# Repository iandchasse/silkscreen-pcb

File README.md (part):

# Silkscreen

**An open-source, open-hardware e-reader mainboard.**

Silkscreen is an open e-paper development board. You can build a pocket reader around it,
adapt its firmware or extend the electronics; this repository covers the mainboard. A factory
can assemble the board for you, and you add a compatible e-paper display, battery, microSD card
and case. It is a 2-layer ESP32-S3 board with a 24-pin display connector,
optional touch and frontlight, microSD and single-cell Li-ion/LiPo power.

It is the successor to [de-link](https://de-link.me). The de-link project hub's pages and photos
are kept on the [`de-link-old`](https://github.com/iandchasse/silkscreen-pcb/tree/de-link-old)
branch. I designed Silkscreen in KiCad 9, but
**you do not need KiCad to order a board.** Every file a factory asks for is in the
`production/` folder of this repository, ready to upload.

| Back (all components) | Front (silkscreen art) |
|:---:|:---:|
|  |  |

## What it is

- **Brain:** an ESP32-S3 module with 16 MB of flash and 8 MB of PSRAM, with USB built in. You
  plug a USB-C cable straight into it, no adapter.
- **Screen:** a 24-pin connector for SPI e-paper panels. The primary target is Good Display's
  4.26" panel family, in plain, touch, frontlight, or touch + frontlight versions. The plain panel
  is sold as `GDEY0426T82`; the others are `GDEQ0426T82` with a suffix for the variant (`-T01C`
  touch, `-FL01C` front light, `-FT01C` both), so always order by the full part number.
- **Power:** charges and runs from a single-cell Li-ion/LiPo pack over USB-C, with charger,
  cell protection and a 3.3 V regulator on board. The charger is a TI BQ21040: about 115 mA, which
  takes about 5 hours for a 500 mAh pack, and only between about 0 and 41 °C, measured by a
  thermistor on the board. Power it from a 5 V source only.
- **Temperature:** 0 to 50 °C in use, a limit set by the display panel.
- **Storage:** a push-push microSD socket.
- **Buttons:** eight page/navigation buttons, plus power and reset.
- **Size:** 60.05 × 111.30 mm, 1.6 mm thick. Every part is soldered onto the **back** face, so
  the front is clear for the display.

Silkscreen is built to run the open firmware made for Xteink's readers, starting with CrossPoint.
Setting them up for this board is closed-beta work, so there is **no firmware release for it
yet**. Read [Firmware](#firmware) before you order.

The complete picture of the project, the story behind it, the cost breakdown and the build
configurator are on the project website, [silkscreenreader.com](https://silkscreenreader.com).
The current [site preview](https://de-link.me/silkscreen-test) includes the builder and beta plans.

Everything about how the board works, pin by pin, is in one document:
[docs/HARDWARE.md](docs/HARDWARE.md). It covers every circuit block, the GPIO map, what firmware
has to do for the hardware, and the dimensions a case needs.

---

## What you need besides the board

The factory sends you a populated circuit board and nothing else. You also need:

| Item | What to get |
|---|---|
| **Display panel** | One of the 4.26" Good Display variants: `GDEY0426T82` (plain), `GDEQ0426T82-T01C` (touch), `-FL01C` (frontlight), `-FT01C` (touch + frontlight). The panel you pick decides which optional parts you fit. See [Choosing a configuration](#choosing-a-configuration). |
| **Battery** | A protected **single-cell** (3.7 V nominal / 4.2 V charged) Li-ion or LiPo pack fitted with a **JST-PH 2.0 mm, 2-pin** plug. Its manufacturer's limits must permit 4.2 V charging at the board's approximately 115 mA charge current (a 500 mAh pack charges in about 5 hours; the charger stops after 10 hours, so a pack above about 1000 mAh may not fill completely at this current, and `R6` = 3.9k gives about 140 mA). Read the polarity note below before you plug it in. I use [this 500 mAh `503035` pack (5 × 30 × 35 mm, JST-PH 2.0)](https://www.amazon.com/dp/B0GDQLLF12). It fits the board's 38.75 × 30.50 mm battery bay snugly. If a cell requires a lower charge current, adjust `R6` and verify the resulting current against its specifications ([HARDWARE.md §3.2](docs/HARDWARE.md#32-battery-charger)). A matching size, plug or protection board alone does not establish compatibility. |
| **microSD card** | Any normal microSD card. The battery normally sits in the board's cut-out directly in front of the card slot, so you lift or slide the cell aside to put a card in or take one out. I designed it that way; the card is not meant to be swapped often. |
| **USB-C cable** | A **data** cable, not a charge-only one, or the board will charge but never appear on your computer. Power the board from a **5 V** USB-C charger or a PC port only. It has no input over-voltage protection and makes no USB-PD request, so a compliant charger stays at 5 V, but a faulty or fixed 9 V or 12 V supply would kill it. |

**Battery lead order.** On the board, `J5` pin 1 is battery **negative** and pin 2 is battery
**positive**, and the board prints **- +** with the word **CHECK** right beside the connector's
mouth. A pack's wire colors are a good guide (black is negative, red is positive), but there is
no industry standard for which side of a JST-PH plug each wire goes in: packs ship both ways
round, and the two look identical in a photo. So before you plug a pack in, with USB unplugged,
check that its black wire lines up with the **-** mark and its red wire with the **+**. If they are
the wrong way round, swap the two wires in the plug
([how to reverse a JST battery plug](https://www.digikey.com/en/maker/blogs/2025/reversing-the-polarity-on-lipo-battery-jst-connectors)).
A multimeter is the surest check.

> [!WARNING]
> Lithium cells are a fire risk if reversed, shorted or crushed. Check your pack against the
> **- +** marks beside `J5` before plugging it in, and measure it if you can. Use a pack with its
> own protection board. Stop using any cell that is puffed, hot or damaged.

**If the board shuts off on battery and stays off.** The board has its own cell protection
(`U5`, `Q1`), which cuts the battery off on an overload or a short; it trips between about 0.83 and
1.68 A. A trip on battery needs USB to clear: plug in USB and the protection resets.

**Screws and case are not on this list.** The board has six M2 mounting holes, but which screws
you need depends on the case you use, and no case is supplied here. See
[The board and your case](#the-board-and-your-case).

---

## Order an assembled board, step by step

> [!CAUTION]
> **Silkscreen has working prototypes, and the closed beta is underway.** This board should work, but
> building one is at your own risk: a mistake I have not found yet could mean a board that does
> not work, and the factory does not refund a board that was built exactly as the files said. If
> you have concerns or questions, join the [Discord](https://discord.gg/zCnKFt4Y4P) before you
> order.
>
> Build your own board to participate; there is no email application. The builder supplies
> the files for your configuration. Check its current firmware support and build instructions
> before ordering.
>
> **If your board has no `R84` resistor** (it was made from older files), power it from a USB-C
> charger, an ordinary USB-A charger or a PC port rather than a fast-charge USB-A brick on a short,
> thick cable ([HARDWARE.md §3.1](docs/HARDWARE.md#31-usb-c-input--protection)), check `J6`'s pins
> with a meter ([§11](docs/HARDWARE.md#11-expansion-header)), and add two wires after a cut (see
> [below](#cutting-the-board-down-for-a-smaller-display)). The files in `production/` are Rev 1.03:
> they add `R84`, ground vias, a 12-pad SMD USB-C socket in place of the through-hole one and a
> charge-enable gate fed from `USB_VBUS` (all from Rev 1.02) and, new in 1.03, a TI BQ21040 charger
> with a temperature sensor in place of the TP4056, resettable fuses on the frontlight, touch,
> e-paper and `J6` pin 7 supplies (`F3` to `F6`), and a current-sense pair for the cell protection
> (`R85`/`R86`). They have not been built yet. (Files labelled Rev 1.01 and Rev 1.02 were published
> on 2026-10-01 and 2026-10-23 and never ordered; Rev 1.03 replaces them.)
>
> Your screen panel and battery are not part of the board order: see
> [What you need besides the board](#what-you-need-besides-the-board). You can start on an
> enclosure design from the STEP model in
> [The board and your case](#the-board-and-your-case); the `#enclosure-design` channel on the
> Discord is where case work is being shared and discussed.

You do not need KiCad and you do not need to know how a PCB is designed. A factory makes the
board and solders every part onto it. You will be clicking through a web shop and uploading three
files that are already in this repository. Unfamiliar words are defined in
[Words used on the factory's website](#words-used-on-the-factorys-website).

> **Or let the builder make the files.** The *Build one* page on the website walks you through
> the panel variant and the optional blocks, estimates what the result costs, and gives you the
> three upload files for exactly that build: the same Gerber zip, plus a BOM and CPL with the
> parts you left off removed (see [Choosing a configuration](#choosing-a-configuration)). For the
> full build they are exactly the files in `production/`. The steps below are the same either way.

### What it costs and how long it takes

The minimum order is **5 bare boards**, and you choose how many of them the factory assembles:
as few as **2**, all 5, or more boards if you want them. Most of the bill is one-off (the bare
boards, setup, the solder stencil, and a small loading fee for each of about thirty "Extended"
part types the factory has to fetch), so the price per assembled board falls quickly as you build
more. The website's cost page breaks the cost down by order size and explains where each fee
comes from.

For scale, my own order (no coupons, US delivery): five boards with two
assembled came to **$223.95** for boards, parts and assembly, and **$305.23** at checkout once
shipping, US tariffs and tax were added. That is about $150 per working board at two, and the
cost page puts the same build at roughly $77 per board with all five assembled and about $50 at
ten. Prices, shipping and import charges move, so treat every figure as an estimate.

| | |
|---|---|
| Time from clicking *order* to the parcel | about **2 to 3 weeks** |
| Not included | display panel, battery, microSD card, case |

### Step 1: get the three files

Download this repository (green **Code** button, then **Download ZIP**) and unzip it. Everything
you need is in the `production/` folder. You upload exactly three files:

| Upload this | What it is | Where it goes |
|---|---|---|
| `production/Silkscreen_Reader_PCB_1.03.zip` | the **Gerber** files: the board itself, meaning copper layers, outline and hole positions | the *Add Gerber file* box |
| `production/jlc_bom.csv` | the **BOM** (bill of materials): the shopping list of parts | the *Add BOM file* box |
| `production/positions.csv` | the **CPL** (also called the centroid or pick-and-place file): where each part sits and which way it faces | the *Add CPL file* box |

Ignore everything else in that folder. These three belong together and come from the same export.
Do not mix one of them with an older copy of another.

### Step 2: order the bare board

1. Sign in at [jlcpcb.com](https://jlcpcb.com), click **Order now**, then **Add Gerber file** and
   choose `Silkscreen_Reader_PCB_1.03.zip`.
2. The viewer draws the board. Confirm it says **2 layers** and about **60 × 111 mm**. If it does
   not, you uploaded the wrong file.
3. Set **PCB Qty = 5**, **Thickness = 1.6 mm**, **Outer Copper Weight = 1 oz**. For **Surface Finish**,
   pick a lead-free one: OSP, LeadFree HASL or ENIG. Don't pick "HASL(with lead)": it isn't
   RoHS-compliant, and selling the device in the EU needs RoHS. ENIG's flat pads also help the
   0.5 mm-pitch connectors. Solder-mask color is your choice.
4. Leave everything else at its default.
5. Scroll the viewer to the board edges and check the USB-C cut-out, the microSD opening and the
   two narrow slots on the outline are open, not filled. The long one is the display-flex slot;
   the short one is at the tongue neck. Both are wider than JLCPCB's 1.0 mm minimum routed-slot
   width, so neither should raise a design-for-manufacture (DFM) message.

### Step 3: turn on assembly

**PCBA** means "printed circuit board assembly": the factory buys the parts and solders them on
for you, instead of shipping you a bare board.

1. Switch **PCB Assembly** on.
2. Choose **Standard**, not Economic. JLCPCB runs two assembly services, and the ESP32-S3 module
   this board is built around can only be placed on **Standard**, so for a complete board Standard
   is the one you need. (If you are happy to hand-solder the module yourself, you could leave it
   off the order and use the cheaper Economic service for everything else. That is an experienced
   builder's choice, not the path I recommend.)
3. Because this board is 60 mm wide and Standard's conveyor wants at least 70 mm, the factory may
   add **snap-off edge rails**: narrow strips of extra board material along the edges for the
   machine to grip. There is nothing for you to design. Expect a small fee in the quote, and snap
   the rails off when the boards arrive.
4. Set **Assembly side: Bottom**. Every part on this board is on the back. If you leave this on
   *Top* you will receive blank boards and a bag of parts.
5. Set the assembly quantity to the number of boards you want built, from 2 up to the number of
   bare boards in the order.
6. Leave **Tooling holes** on *Added by JLCPCB*.
7. Set **Confirm Parts Placement** to **Yes**. It costs a small fee and is worth it on a first
   order: it lets you look at a picture of where each part will go before the machine runs.
8. Click **Confirm**, then **Next**.

### Step 4: upload the parts list

1. **Add BOM file**: `production/jlc_bom.csv`
2. **Add CPL file**: `production/positions.csv`
3. Click **Process BOM & CPL**.

### Step 5: check the parts the factory picked

You get a table with one row per part. Most rows will be matched.

- **Rows with a blank part number are meant to be blank.** These references (`TP3 TP4 TP5`,
  `R43 R45 R58 R66 R72 R74`, `SW6` and `U13`, the alternate clock chip; the board uses `U14`) are
  tagged *"DNP (standard build)"*. **DNP** means "do not populate": a spot on the board
  deliberately left empty. **Leave them unselected.**
- **Every other row must show a match.** If a row says *No Parts Selected* or *out of stock*, or
  shows a manufacturer's part number instead of an **LCSC code** (the `C…` number that identifies a
  part in the factory's own warehouse), click **Search** and look it up.
  [`fabrication/BOM.md`](fabrication/BOM.md) lists an approved alternative for every part on this
  board. Use that list rather than picking a look-alike yourself, because several of these parts
  have near-identical siblings with different pinouts.
- The part most often short is **TPS923610DRLR** (`U10`, LCSC `C52919131`), the frontlight driver.
  Check its stock (JLCPCB had 80 on 2026-11-05). If you are not fitting a frontlight panel, untick it along with the rest of the
  *Frontlight* group in [Choosing a configuration](#choosing-a-configuration). If you *are* fitting
  one and it is out of stock, see [If the frontlight driver is out of stock](#if-the-frontlight-driver-is-out-of-stock).
- The clock `U14` (RV-8263-C7, LCSC `C5137460`) is also thinly stocked (1,058 on 2026-11-05). The
  reader runs without a clock, so if it is out of stock you can leave it off, or fit the DS3231MZ+TRL
  (`C107410`) at `U13` instead and leave `U14` off.
- If you are deliberately leaving a block off, remove its parts from the BOM **and** the CPL, or
  untick them here.
- Click **Next**.

#### If the frontlight driver is out of stock

JLCPCB's stock of the TPS923610DRLR comes and goes, and restocking is unpredictable. It isn't a
dead end, just a slower one. In order of preference:

1. **Pre-order it through JLCPCB.** Any account can do this; it just takes lead time. While LCSC
   lists several suppliers for this part, the wait should be short.
   1. Sign in to JLCPCB and open **Parts Manager → Order Parts**.
   2. Search `C52919131`. Enter the quantity you need, plus one or two spares, and add it to
      **My Parts Lib**.
   3. Go to the cart and check out within the hour, or the cart is cancelled. JLCPCB emails the final
      price within 48 hours and refunds or charges the difference.
   4. Wait until the parts reach JLCPCB's warehouse. Pre-ordered parts can't be used before then,
      and they are never shipped to you; they only go into your assembly orders.
   5. Place the board order as above. At Step 5, `U10` matches from your private library.

   JLCPCB's own guide: [What is JLCPCB Parts Pre-order Service?](https://jlcpcb.com/help/article/What-is-JLCPCB-Parts-Pre-order-Service)
   · [Pre-ordering terms](https://jlcpcb.com/help/article/pre-ordering-parts-terms-conditions)

2. **If you can't pre-order it, swap two parts, not one:**

   | Ref | Stock part | Swap to |
   |---|---|---|
   | `U10` | TPS923610DRLR | **TPS923611DRLR** |
   | `D3` | SMAJ26A | **SMAJ33A** |

   The TPS923611 shares the TPS923610's datasheet, package (SOT-563, `DRL`), pinout and 1.8 A switch
   limit, so it fits the same footprint. The one difference is its output ceiling: about 30 V, with
   over-voltage protection at 29.6–31.4 V, where the TPS923610 stops at about 24.5 V. The stock
   `D3`, an SMAJ26A clamp on `LED_SW`, starts conducting at 28.9 V. With a TPS923611 and the stock
   `D3`, a disconnected light lets the driver push current into `D3` before its own protection trips,
   and `D3` can burn out. An SMAJ33A doesn't conduct until about 36.7 V, so the driver's protection
   trips first. Don't leave `D3` off instead: it protects the light connectors (`J3`, `J6`).

   Treat this as the second choice. Its higher ceiling leaves `C9` charged to a higher voltage after an open-load
   trip, so with one light string open and the other intact, a colour change dumps a larger pulse into the driver's
   feedback pin. [HARDWARE.md §13.1](docs/HARDWARE.md#131-firmware-contract--things-the-board-needs-firmware-to-do)
   lists the firmware rule that avoids it; if you can wait for a pre-order, do that instead.

   The **TPS923612** is not an option: it only comes in a 2 × 2 mm WSON (`DRV`) package, which
   doesn't fit this footprint.

### Step 6: check the placement preview (do not skip this)

You see a drawing of the board with every part on it. This is your last chance to catch a part
that is rotated wrongly. A matched part code does not prove the part is the right way round.
The parts below are the ones most often turned or offset in JLCPCB's preview; check them.

| Part | What to check |
|---|---|
| `D2` | The USB power LED. **Pad 1, the end next to `R59`, is the cathode.** JLCPCB's part numbers the anode as pin 1, so if the preview shows a pin-1 dot on `D2`, it belongs at the other end (`USB_VBUS`). The placement file already turns the part to suit: don't rotate it to put the dot on pad 1. |
| `U2`, `U5`, `D8`, `U11` | Small 3 to 8 pin chips (`U11` is the BQ21040 charger). Check their rotation. |
| `U14` | The clock chip: eight small pads in two rows of four. JLCPCB's library draws this part at 90° to KiCad's footprint, so the placement file rotates it; check that its pads line up. |
| `U10` | The frontlight driver, 6 pins in two rows of 3. Pin 1 (the `/LED_VIN` net, behind the fuse `F3`) is the corner at (50.24, 121.50) in the KiCad file; pin 4 (`GND`) is diagonally opposite. |
| `F3`–`F6`, `R85`/`R86`, `TH1`, `C38` | The new two-pad parts: four fuses (0603), two sense resistors (1206), the thermistor and a capacitor. None has a polarity; check that each one sits centered on its pads. |
| `D3`–`D6` | The polarized diodes: the SMAJ26A (`D3`) and the three B5819W (`D4`, `D5`, `D6`). **Pad 1 is the cathode (the bar end) on all four.** |
| `J4` | The touch connector. It should sit on its pads; the pads are what matter. |
| `J1` | The USB-C socket: twelve small pads in a row, two pegs and four shield slots. It should sit on its pads with the opening facing the board edge. JLCPCB's library footprint has a different origin from KiCad's, so the placement file carries a 1.305 mm correction for it; check that it is not shifted and that the opening faces the board edge. |
| `U4`, `J7` | The ESP32 module and the microSD socket. Check they are centered on their pad patterns. |

If something looks wrong, use the preview's rotate and move tools to fix it, and **save a
screenshot of the corrected preview**. Click **Next**.

### Step 7: through-hole parts, soldered by the factory or by you

Several parts have legs that pass through the board rather than sitting on its surface. That is
**THT** (through-hole technology), as opposed to **SMD** (surface-mount) for everything else. They
are the battery connector `J5`, the expansion header `J6` and the ten buttons `SW1` to `SW5` and
`SW7` to `SW11`. They are already in the files you uploaded, so this is
a choice, not extra work:

- **Let the factory solder them.** JLCPCB charges a one-off hand-soldering fee plus a small amount
  per joint, which comes to about **$0.90 per assembled board** on top of the fee. It adds about a
  day. Confirm on the quote page that through-hole soldering
  appears as a line item.
- **Solder them yourself.** You get the parts loose and solder them yourself: the JST battery
  connector, the 12-pin expansion header and the buttons. Worth doing if you own a decent iron.
  (The USB-C socket `J1` is an SMD part and is not in this list; on a hand-built board it is the
  fiddly one, with twelve small pads and four shield tabs. Each pad has a 0.3 mm tail of bare copper behind
  the socket for the iron, so keep the tip off the plastic. Solder the tabs too: they carry the
  plugging force.)

### Step 8: pay, and keep the paperwork

Read the price summary: bare boards, setup fee, per-part-type fees, the parts themselves,
assembly. Place the order. Then keep in one folder the order confirmation, the accepted BOM as the
factory matched it, any substitutions it proposed, and your screenshot of the approved placement
preview. If you order again, you will want to know exactly what was built the first time.

### Using a different factory (PCBWay, NextPCB, others)

Nothing in the design is tied to JLCPCB. Upload files for other assemblers are kept in
[`production/other_fabs/`](production/other_fabs/): a PCBWay BOM with KiCad's own placement file, a
NextPCB BOM and centroid file in NextPCB's template (plus SMD-only and through-hole-only pairs in
`split/`), and a bottom-side assembly drawing. They use the same Gerber zip as the JLCPCB order and
are generated from the design with:

```bash
python fabrication/make_fab_files.py --split
```

Know what you are taking on, though. **JLCPCB is the only factory I have ordered
boards from.** I have not ordered from NextPCB or PCBWay. Another factory is a fine choice if you
prefer one. You will be doing the part matching, the rotation check and the back-and-forth with
their engineers yourself, without a known-good order to compare against. Everything else in this
guide assumes JLCPCB.

---

## Choosing a configuration

The files in `production/` are the **full build**: every block fitted except the DNP options.
The board is a **core** that is always fitted, plus add-on groups you can leave off. For
a reduced configuration, download its files from the builder on the website, or do it by hand:
delete the listed references from the BOM **and** the CPL and leave the pads empty.

Each group lists every part that exists only to serve it, so leaving a group off leaves nothing
behind that does no work. The website's builder uses the same groups.

| Group | References | Fit it when | Works without it? |
|---|---|---|---|
| **Core** (always) | Everything not listed below: ESP32-S3 `U4`, USB-C `J1`/`U6` and protection, charger `U11` with its thermistor `TH1`, cell protection `U5`/`Q1`/`Q3`/`Q8` with its sense resistors `R85`/`R86`, power mux `U2`, LDO `U3` with its input capacitor `C4`, battery monitor, microSD `J7`/`Q7`/`U1`/`U9`, the 24-pin display connector `J2` with its charge pump and boost (`L1`, `Q4`, `D4`-`D6`, `R14`, ...) and the boost's fuse `F6`, power button `SW10`, reset `SW11`, LED `D2`, and the I²C pull-ups `R47`/`R48` (shared by touch, clock and `J6`) | Always | This is the minimum working board |
| **Touch** | `J4`, `U7`, the supply fuse `F4`, jumpers `R44 R46 R52` | The panel has a touch layer (`-T01C`, `-FT01C`) | Yes: omit the whole block on a non-touch panel |
| **Frontlight** | driver `U10` with its supply fuse `F3`, `L2`, input capacitor `C12` and output capacitor `C9`; current set `R37`; warm/cool select `Q5`, `Q6`, `U12` (with its decoupling `C24`) and `R75`; LED monitor `R39`, `R41`, `C31`; string bleeders `R49`, `R50`; output clamps `D3`, `D8` (`TP3`-`TP5` stay DNP) | The panel has a frontlight (`-FL01C`, `-FT01C`), or you want to drive a compatible external light through `J6` or `J3` | Yes: omit if the panel has no bonded light and you do not want an external light |
| **Frontlight connector** | `J3` | Fit with the frontlight driver, for a bonded panel light or compatible external-light flex PCB (in development) | Omit with the driver |
| **Expansion header** | `J6`, `U8`, `CR2`, `CR3`, `F2`, `F5`, and the GPIO series resistors `R65 R68 R69` | You want spare GPIO, I²C and the external-light output | Yes |
| **Real-time clock** | `U14`, `C30` (or `U13` instead of `U14`) | You want the time kept | Yes: the reader runs without it, and it can be added later by hand |
| **Alternate RTC** | `U13` (**not fitted in the full build**) | You want the more accurate clock (±5 ppm, temperature-compensated, against ±20 ppm) instead of `U14`; it costs about $1.8 more per board at 30 boards | Fit **one** clock or none; their I²C addresses differ (`0x51` and `0x68`), so there is no bus conflict, but a second clock is wasted money |
| **Side page-turn keys** | per key: `SW1`+`R61` (right-down), `SW4`+`R11` (right-up), `SW7`+`R36`+`R73` (left-up), `SW5`+`R35` (left-down); with any side key, the ladder's pull-up `R28` and filter `C28` | Your case has side keys | Yes: fit any subset |
| **Bottom-row keys** | per key: `SW2`+`R60`, `SW3`+`R18`, `SW8`+`R19`, `SW9`+`R20`; with any bottom key, the ladder's pull-up `R4` and filter `C27` | Your case has bottom keys | Yes: fit any subset; with touch you can drop most keys |

Notes:

- **The panel choice drives touch and frontlight.** The four 4.26" Good Display variants are
  `GDEY0426T82` (plain), `GDEQ0426T82-T01C` (touch), `-FL01C` (frontlight) and `-FT01C` (touch +
  frontlight).
  Fit the touch parts only for a touch variant. Fit the frontlight driver and `J3` for a light
  variant, or keep both for a compatible external light on a plain or touch-only panel.
- **`U8`, `CR2`, `CR3`, `F2` and `F5` are `J6`'s own protection and come off with it.** `U8` protects only
  `J6` pins; `CR2` and `CR3` clamp the 3V3 and raw-battery pins where they leave the board, and the
  resettable fuses `F5` (3V3 pin) and `F2` (battery pin) sit in series with those pins and feed nothing else. The 33 Ω
  series resistors `R65`/`R68`/`R69` only reach `J6` too; they cost nothing, so leaving them fitted
  on a header-less board is harmless. Do **not** remove `U9`, `D3` or `D8` with `J6`. `U9` also
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
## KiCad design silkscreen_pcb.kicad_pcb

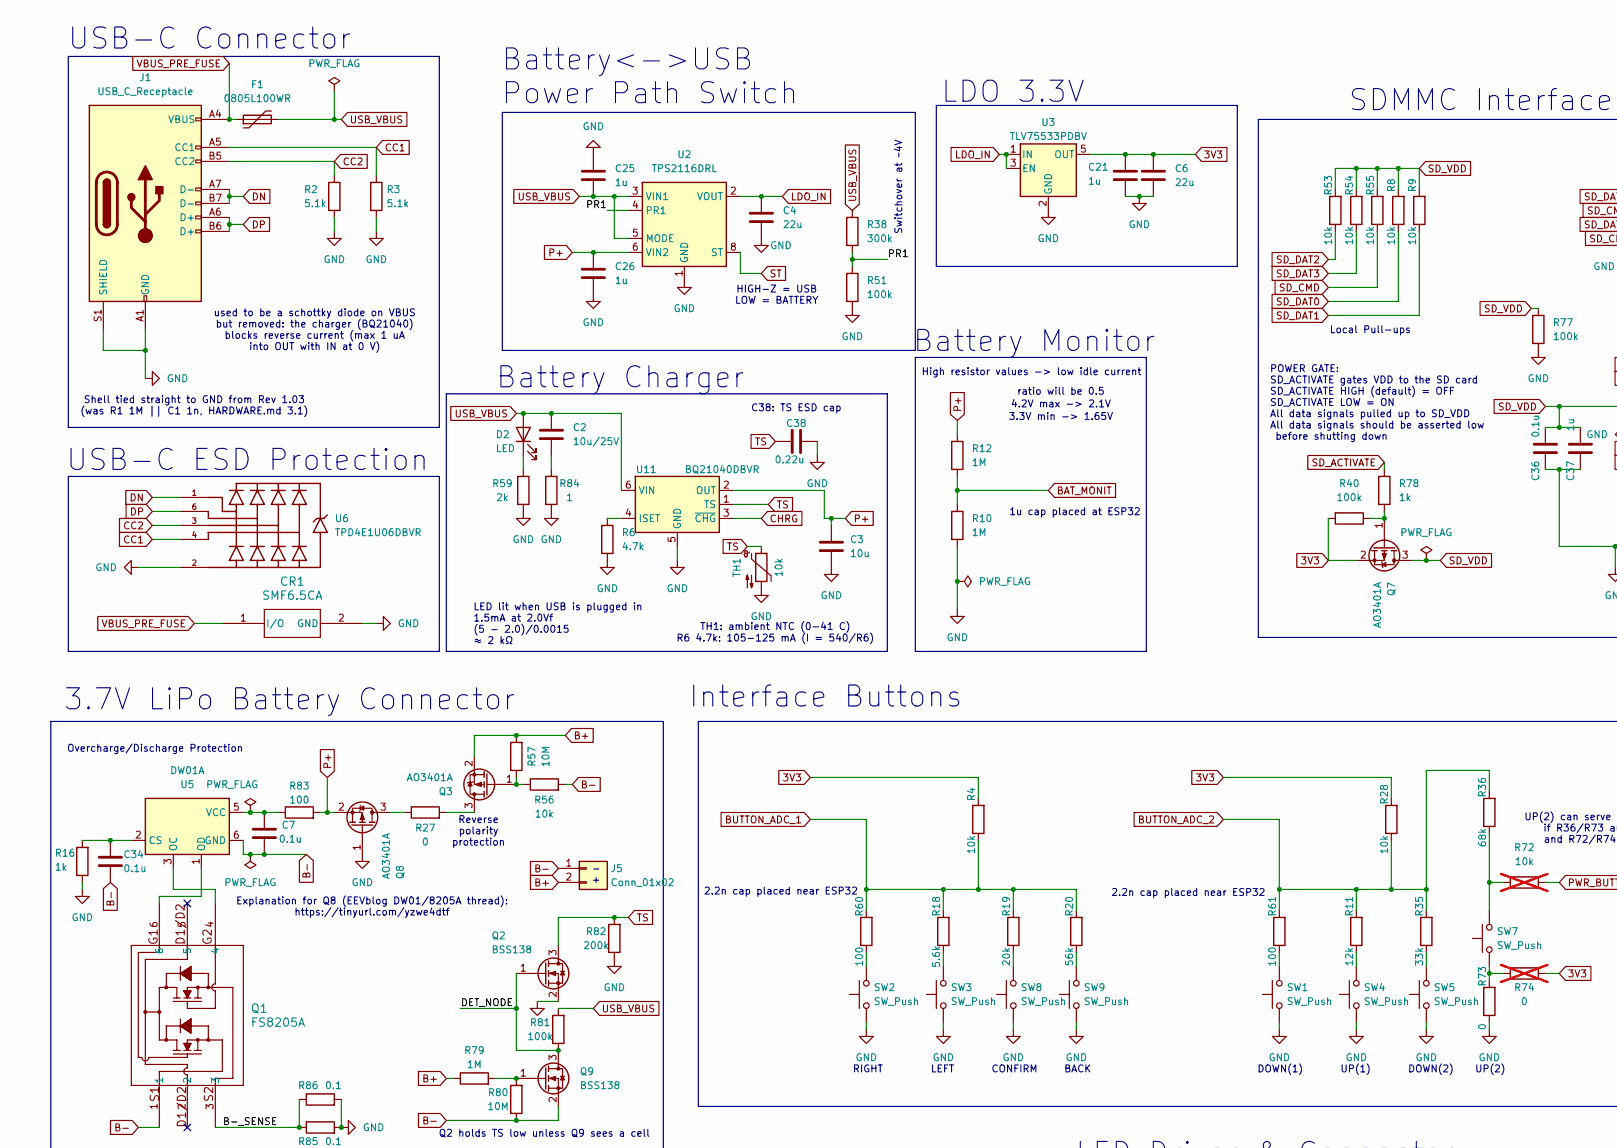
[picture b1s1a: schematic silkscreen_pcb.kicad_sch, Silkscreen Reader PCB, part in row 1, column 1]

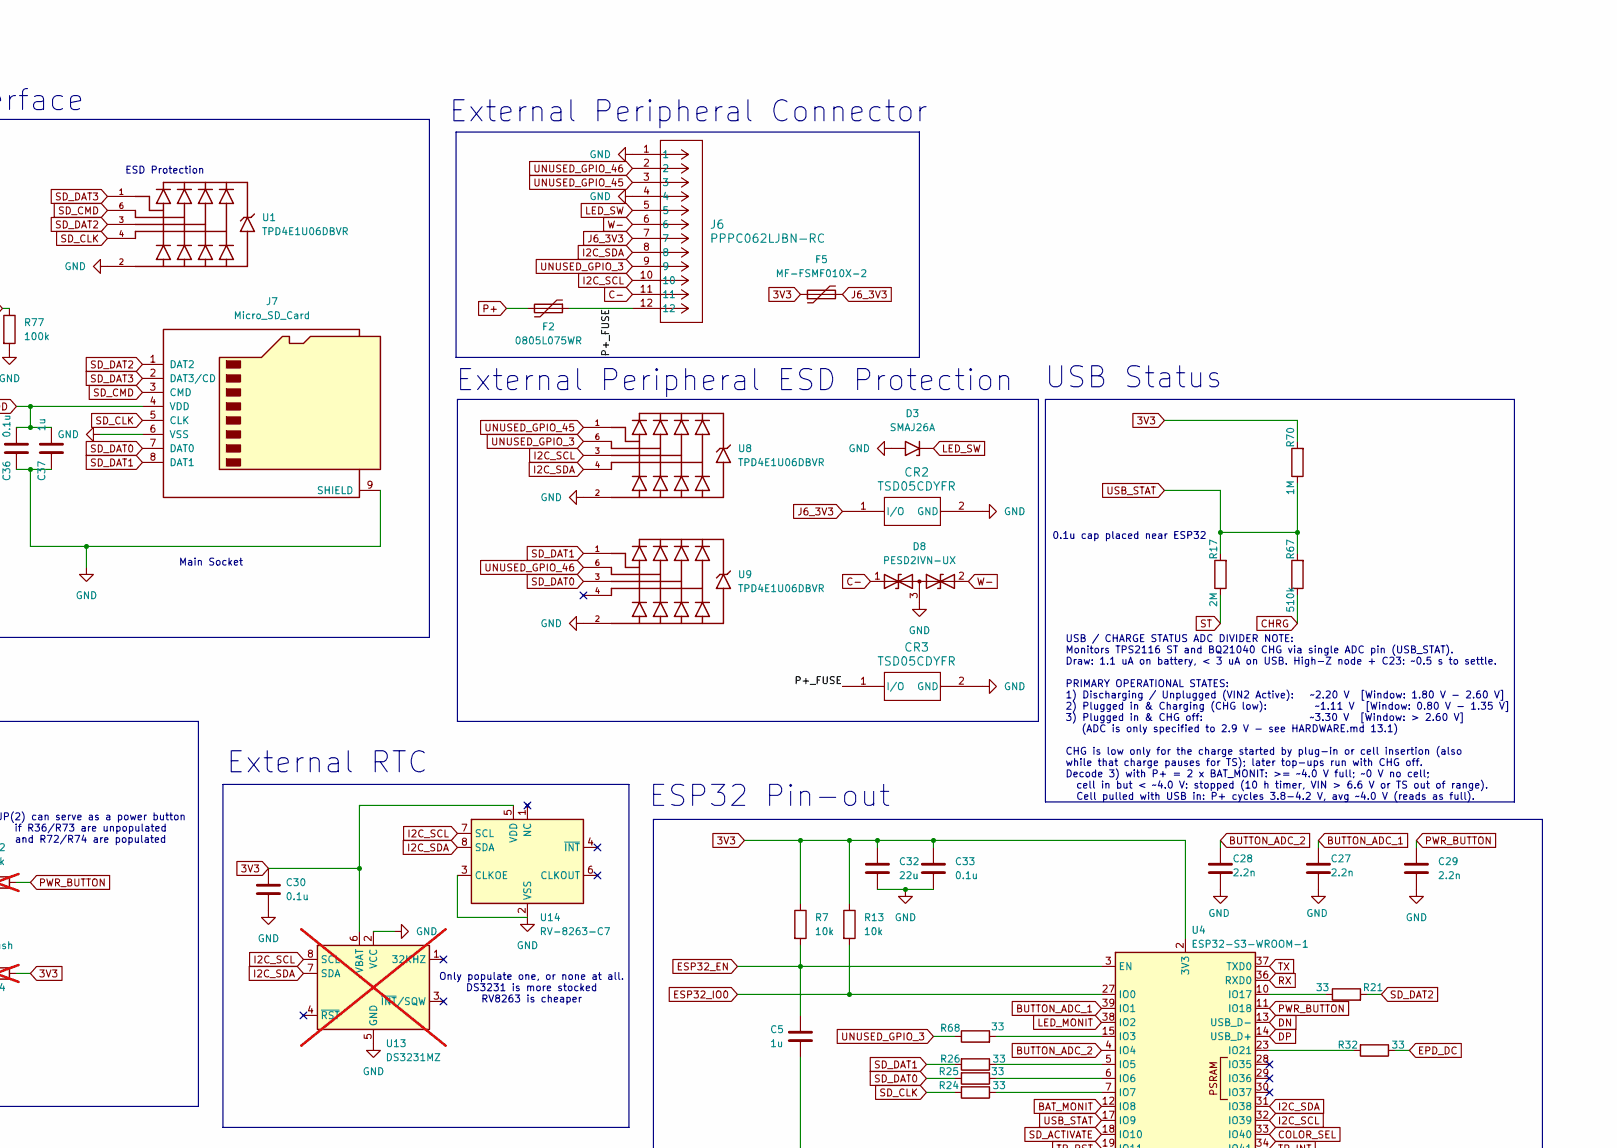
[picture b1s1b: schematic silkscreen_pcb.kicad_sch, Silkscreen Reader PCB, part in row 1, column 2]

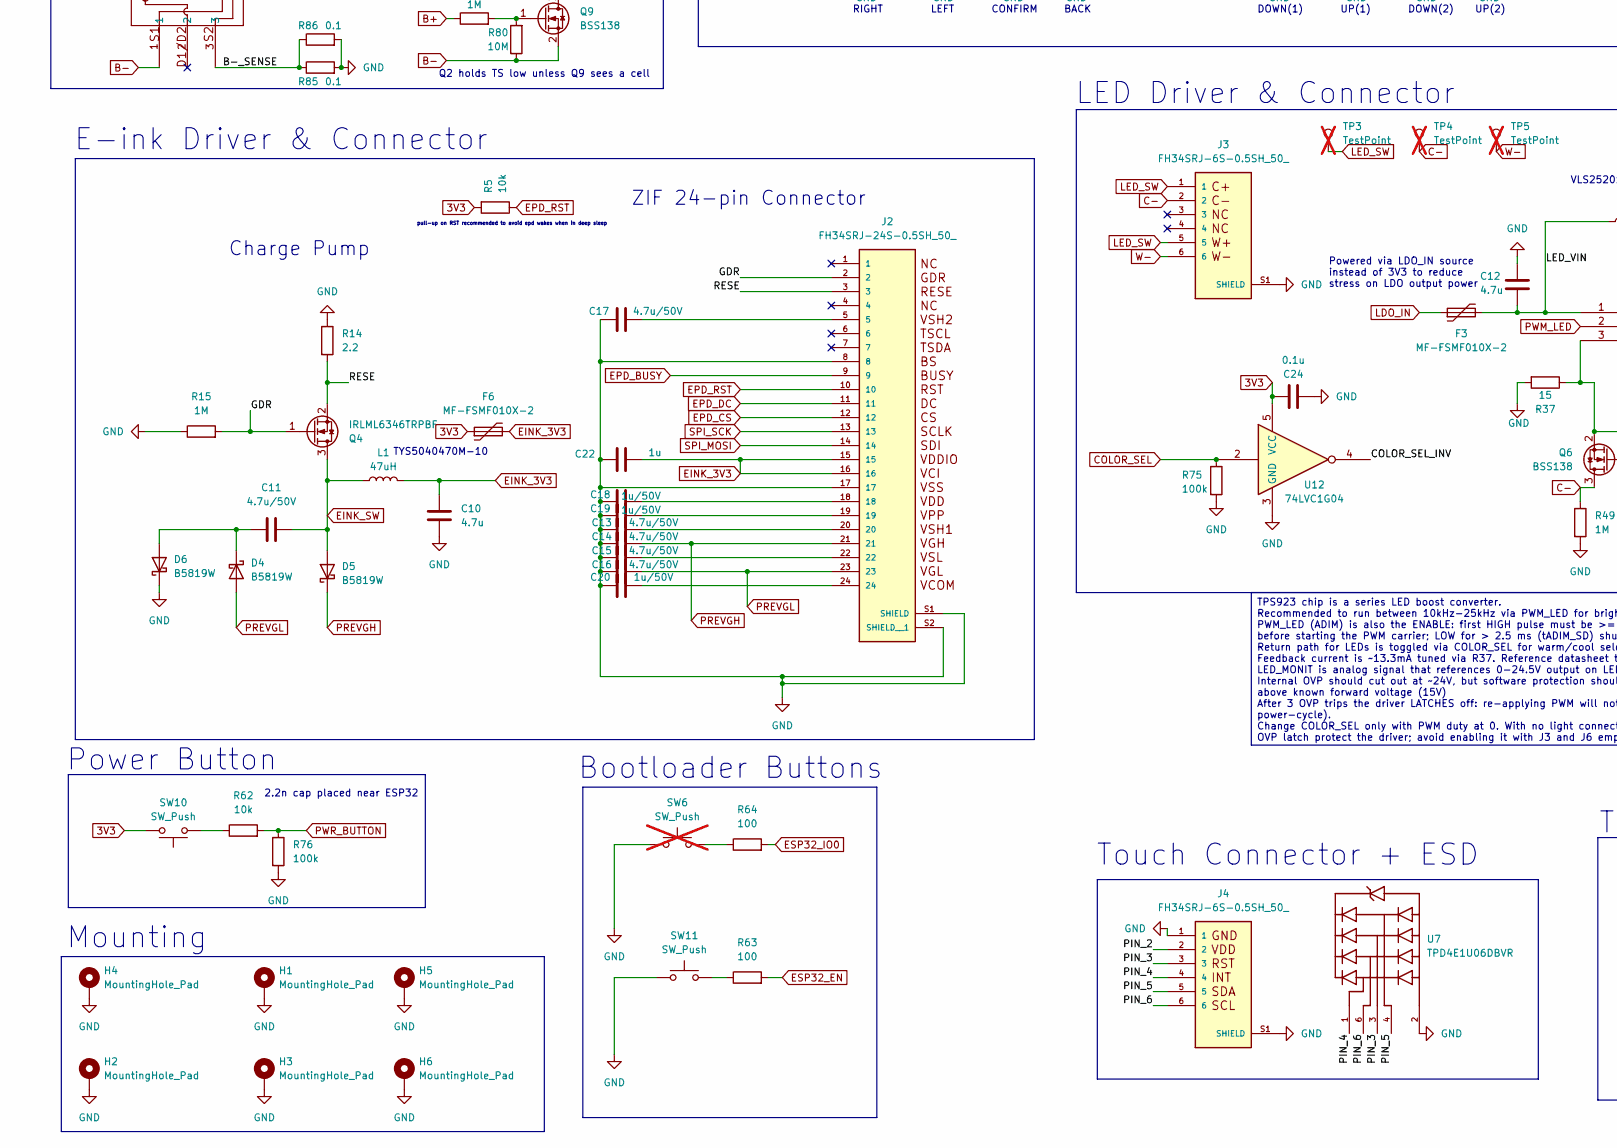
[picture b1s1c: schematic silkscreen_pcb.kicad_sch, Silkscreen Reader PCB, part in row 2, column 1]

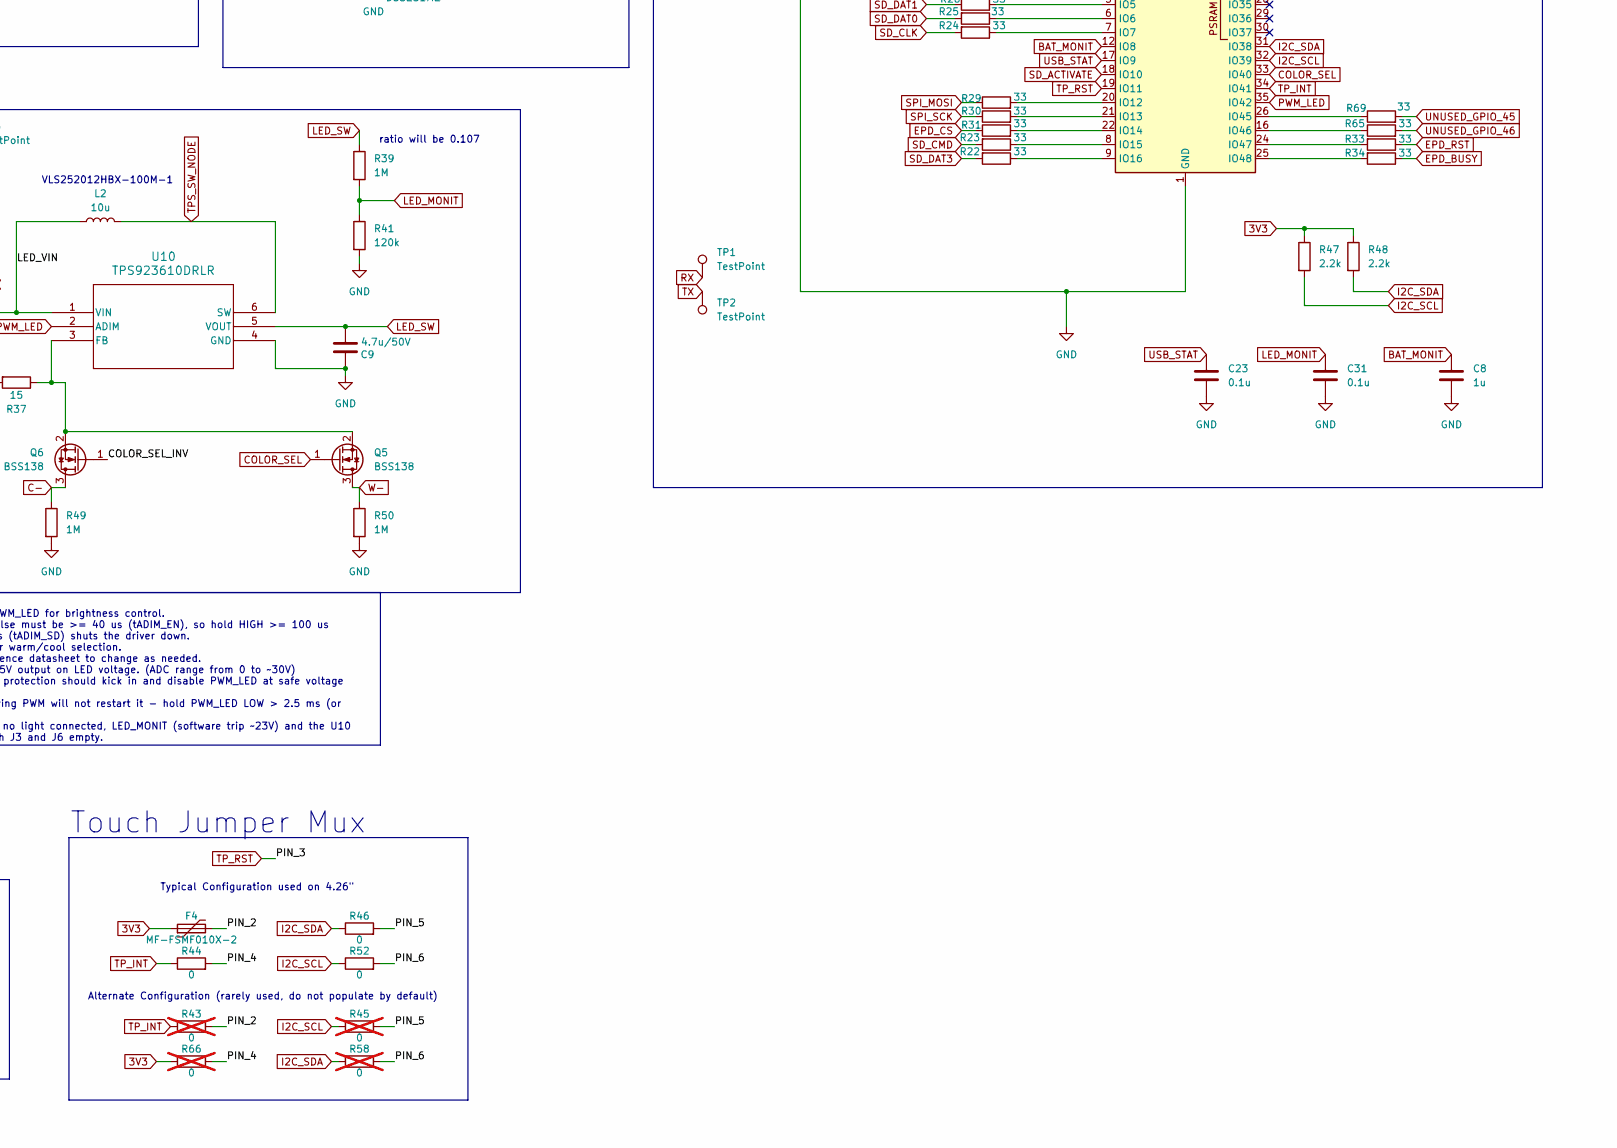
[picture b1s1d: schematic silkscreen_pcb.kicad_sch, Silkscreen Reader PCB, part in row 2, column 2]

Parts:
C2: 10u/25V; C_0603_1608Metric_Pad1.08x0.95mm_HandSolder; MPN CL10A106MA8NRNC; LCSC C96446
C3: 10u; C_0603_1608Metric_Pad1.08x0.95mm_HandSolder; MPN CL10A106KP8NNNC; LCSC C19702
C4, C6, C32: 22u; C_0805_2012Metric_Pad1.18x1.45mm_HandSolder; MPN GRM21BR61E226ME44L; LCSC C45783
C5, C8, C21, C22, C25, C26, C37: 1u; C_0603_1608Metric_Pad1.08x0.95mm_HandSolder; MPN CL10A105KB8NNNC; LCSC C15849
C7, C23, C24, C30, C31, C33, C34, C36: 0.1u; C_0603_1608Metric_Pad1.08x0.95mm_HandSolder; MPN CC0603KRX7R9BB104; LCSC C14663
C9, C11, C13, C14, C15, C16, C17: 4.7u/50V; C_0805_2012Metric_Pad1.18x1.45mm_HandSolder; MPN CL21A475KBQNNNE; LCSC C513770
C10, C12: 4.7u; C_0603_1608Metric_Pad1.08x0.95mm_HandSolder; MPN CL10A475KO8NNNC; LCSC C19666
C18, C19, C20: 1u/50V; C_0805_2012Metric_Pad1.18x1.45mm_HandSolder; MPN CL21B105KBFNNNE; LCSC C28323
C27, C28, C29: 2.2n; C_0603_1608Metric_Pad1.08x0.95mm_HandSolder; MPN CL10B222KB8NNNC; LCSC C1604
C38: 0.22u; C_0603_1608Metric_Pad1.08x0.95mm_HandSolder; MPN CC0603KRX7R9BB224; LCSC C21120
CR1: SMF6.5CA; D_SMF; MPN SMF6.5CA; LCSC C19077501
CR2, CR3: TSD05CDYFR; D_SOD-323_HandSoldering; MPN TSD05CDYFR; LCSC C5299440
D2: LED; LED_1206_3216Metric_Pad1.42x1.75mm_HandSolder; MPN LTST-C150KRKT; LCSC C28310439
D3: SMAJ26A; D_SMA; MPN SMAJ26A; LCSC C19077543
D4, D5, D6: B5819W; D_SOD-123; MPN 1N5819HW-7-F; LCSC C8598
D8: PESD2IVN-UX; SOT-323_SC-70_Handsoldering; MPN PESD2IVN-UX; LCSC C42370512
F1: 0805L100WR; Fuse_0805_2012Metric_Pad1.15x1.40mm_HandSolder; MPN 0805L100WR; LCSC C269106
F2: 0805L075WR; Fuse_0805_2012Metric_Pad1.15x1.40mm_HandSolder; MPN 0805L075WR; LCSC C269105
F3, F4, F5, F6: MF-FSMF010X-2; Fuse_0603_1608Metric_Pad1.05x0.95mm_HandSolder; MPN MF-FSMF010X-2; LCSC C210355
H1, H2, H3, H4, H5, H6: MountingHole_Pad; MountingHole_2.2mm_M2_DIN965_Pad_TopBottom
J1: USB_C_Receptacle; USB_C_Receptacle_GCT_USB4105-xx-A_16P_TopMnt_Horizontal; MPN USB4105-GF-A; LCSC C2765186
J2: FH34SRJ-24S-0.5SH_50_; HRS_FH34SRJ-24S-0.5SH_50_; MPN FH34SRJ-24S-0.5SH(50); LCSC C324726
J3, J4: FH34SRJ-6S-0.5SH_50_; HRS_FH34SRJ-6S-0.5SH_50_; MPN FH34SRJ-6S-0.5SH(50); DigiKey_Part_Number H125773CT-ND
J5: Conn_01x02; JST_PH_S2B-PH-K_1x02_P2.00mm_Horizontal; MPN S2B-PH-K-S(LF)(SN); LCSC C48579993
J6: PPPC062LJBN-RC; CONN_PPPC062LJBN-RC_SUL; MPN PPPC062LJBN-RC; LCSC C5333437
J7: Micro_SD_Card; microSD_PushPush_TFPUSH-MEM2075; MPN MEM2075-00-140-01-A; LCSC C393941
L1: 47uH; L_APV_ANR5040; MPN TYS5040470M-10; LCSC C206267
L2: 10u; L_1008_2520Metric_Pad1.43x2.20mm_HandSolder; MPN VLS252012HBX-100M-1; LCSC C88532
Q1: FS8205A; SOT-23-6_Handsoldering; MPN FS8205A; LCSC C2830320
Q2: BSS138; SOT-23_Handsoldering; MPN BSS138LT1G; LCSC C7420339
Q3, Q7, Q8: AO3401A; SOT-23_Handsoldering; MPN AO3401A; LCSC C15127
Q4: IRLML6346TRPBF; SOT-23; MPN IRLML6346TRPBF; LCSC C67276
Q5, Q6, Q9: BSS138; SOT-23; MPN BSS138LT1G; LCSC C7420339
R2, R3: 5.1k; R_0603_1608Metric_Pad0.98x0.95mm_HandSolder; MPN RC0603FR-075K1L; LCSC C23186
R4, R5, R7, R8, R9, R13, R28, R53, R54, R55, R56, R62: 10k; R_0603_1608Metric_Pad0.98x0.95mm_HandSolder; MPN RC0603FR-0710KL; LCSC C25804
R6: 4.7k; R_0603_1608Metric_Pad0.98x0.95mm_HandSolder; MPN RC0603FR-074K7L; LCSC C23162
R10, R12, R15, R39, R49, R50, R70, R79: 1M; R_0603_1608Metric_Pad0.98x0.95mm_HandSolder; MPN RC0603FR-071ML; LCSC C22935
R11: 12k; R_0603_1608Metric_Pad0.98x0.95mm_HandSolder; MPN RC0603FR-0712KL; LCSC C22790
R14: 2.2; R_0603_1608Metric_Pad0.98x0.95mm_HandSolder; MPN RC0603FR-072R2L; LCSC C22939
R16, R78: 1k; R_0603_1608Metric_Pad0.98x0.95mm_HandSolder; MPN RC0603FR-071KL; LCSC C21190
R17: 2M; R_0603_1608Metric_Pad0.98x0.95mm_HandSolder; MPN RC0603FR-072ML; LCSC C22976
R18: 5.6k; R_0603_1608Metric_Pad0.98x0.95mm_HandSolder; MPN RC0603FR-075K6L; LCSC C23189
R19: 20k; R_0603_1608Metric_Pad0.98x0.95mm_HandSolder; MPN RC0603FR-0720KL; LCSC C4184
R20: 56k; R_0603_1608Metric_Pad0.98x0.95mm_HandSolder; MPN RC0603FR-0756KL; LCSC C23206
R21, R22, R23, R24, R25, R26, R29, R30, R31, R32, R33, R34, R65, R68, R69: 33; R_0603_1608Metric_Pad0.98x0.95mm_HandSolder; MPN RC0603FR-0733RL; LCSC C23140
R27: 0; R_0805_2012Metric_Pad1.20x1.40mm_HandSolder; MPN RC0805JR-070RL; LCSC C17477
R35: 33k; R_0603_1608Metric_Pad0.98x0.95mm_HandSolder; MPN RC0603FR-0733KL; LCSC C4216
R36: 68k; R_0603_1608Metric_Pad0.98x0.95mm_HandSolder; MPN RC0603FR-0768KL; LCSC C23231
R37: 15; R_0603_1608Metric_Pad0.98x0.95mm_HandSolder; MPN RC0603FR-0715RL; LCSC C22810
R38: 300k; R_0603_1608Metric_Pad0.98x0.95mm_HandSolder; MPN RC0603FR-07300KL; LCSC C23024
R40, R51, R75, R76, R77, R81: 100k; R_0603_1608Metric_Pad0.98x0.95mm_HandSolder; MPN RC0603FR-07100KL; LCSC C25803
R41: 120k; R_0603_1608Metric_Pad0.98x0.95mm_HandSolder; MPN RC0603FR-07120KL; LCSC C25808
R43, R45, R58, R66, R74: 0; R_0603_1608Metric_Pad0.98x0.95mm_HandSolder; MPN RC0603JR-070RL; LCSC C21189; not fitted
R44, R46, R52, R73: 0; R_0603_1608Metric_Pad0.98x0.95mm_HandSolder; MPN RC0603JR-070RL; LCSC C21189
R47, R48: 2.2k; R_0603_1608Metric_Pad0.98x0.95mm_HandSolder; MPN RC0603FR-072K2L; LCSC C4190
R57, R80: 10M; R_0603_1608Metric_Pad0.98x0.95mm_HandSolder; MPN RC0603FR-0710ML; LCSC C7250
R59: 2k; R_0603_1608Metric_Pad0.98x0.95mm_HandSolder; MPN RC0603FR-072KL; LCSC C22975
R60, R61, R63, R64, R83: 100; R_0603_1608Metric_Pad0.98x0.95mm_HandSolder; MPN RC0603FR-07100RL; LCSC C22775
R67: 510k; R_0603_1608Metric_Pad0.98x0.95mm_HandSolder; MPN RC0603FR-07510KL; LCSC C23192
R72: 10k; R_0603_1608Metric_Pad0.98x0.95mm_HandSolder; MPN RC0603FR-0710KL; LCSC C25804; not fitted
R82: 200k; R_0603_1608Metric_Pad0.98x0.95mm_HandSolder; MPN RC0603FR-07200KL; LCSC C25811
R84: 1; R_0603_1608Metric_Pad0.98x0.95mm_HandSolder; MPN RC0603FR-071RL; LCSC C22936
R85, R86: 0.1; R_1206_3216Metric_Pad1.30x1.75mm_HandSolder; MPN RL1206FR-070R1L; LCSC C25334
SW1, SW2, SW3, SW4, SW5, SW8, SW9, SW11: SW_Push; MJTP1117_FG; MPN MJTP1117; LCSC C557598
SW6: SW_Push; SW_PUSH_1P1T_6x3.5mm_H4.3_APEM_MJTP1243; MPN MJTP1243; not fitted
SW7, SW10: SW_Push; MJTP1117; MPN MJTP1117; LCSC C557598
TH1: 10k; R_0603_1608Metric_Pad0.98x0.95mm_HandSolder; MPN NCP18XH103F03RB; LCSC C13564
TP1, TP2: TestPoint; TestPoint_Pad_1.0x1.0mm
TP3, TP4, TP5: TestPoint; PinHeader_1x01_P2.54mm_Vertical; not fitted
U1, U6, U7, U8, U9: TPD4E1U06DBVR; SOT-23-6_Handsoldering; PARTREV D; DigiKey_Part_Number 296-35965-1-ND
U2: TPS2116DRL; SOT-583-8; MPN TPS2116DRLR; LCSC C3235557
U3: TLV75533PDBV; SOT-23-5_HandSoldering; MPN TLV75533PDBVR; LCSC C404027
U4: ESP32-S3-WROOM-1; MPN ESP32-S3-WROOM-1-N16R8; LCSC C2913202
U5: DW01A; SOT-23-6_Handsoldering; MPN DW01A; LCSC C351410
U10: TPS923610DRLR; U_DRL0006A_6L_TI-LAND; MPN TPS923610DRLR; LCSC C52919131
U11: BQ21040DBVR; SOT-23-6_Handsoldering; MPN BQ21040DBVR; LCSC C202311
U12: 74LVC1G04; SOT-23-5_HandSoldering; MPN SN74LVC1G04DBVR; LCSC C7827
U13: DS3231MZ; SOIC-8_3.9x4.9mm_P1.27mm; MPN DS3231MZ+TRL; LCSC C107410; not fitted
U14: RV-8263-C7; MicroCrystal_C7_SON-8_1.5x3.2mm_P0.9mm; MPN RV-8263-C7-32.768KHZ-20PPM-TA-QA; LCSC C5137460

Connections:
3V3: C6.1, C21.1, C24.1, C30.1, C32.1, C33.1, F4.1, F5.1, F6.1, Q7.2 (S), R4.2, R5.2, R7.1, R13.1, R28.2, R40.2, R47.1, R48.1, R66.1, R70.2, R74.1, SW10.2, U3.5 (OUT), U4.2 (3V3), U12.5 (VCC), U13.6 (VBAT), U14.5 (VDD)
/B-_SENSE: Q1.3, R85.1, R86.1
/COLOR_SEL_INV: Q6.1 (G), U12.4
/DET_NODE: Q2.1 (G), Q9.3 (D), R81.1
/GDR: J2.2, Q4.1 (G), R15.2
/LED_VIN: C12.2, F3.2, L2.1, U10.1 (VIN)
/P+_FUSE: CR3.1 (I/O), F2.1, J6.12
/PIN_2: F4.2, J4.2, R43.2
/PIN_4: J4.4, R44.2, R66.2, U7.1
/PIN_5: J4.5, R45.2, R46.2, U7.4
/PIN_6: J4.6, R52.2, R58.2, U7.6
/PR1: R38.2, R51.1, U2.4 (PR1)
/RESE: J2.3, Q4.2 (S), R14.2
B+: J5.2, Q3.2 (S), R57.2, R79.1
B-: C7.2, C34.2, J5.1, Q1.1, Q9.2 (S), R56.2, R80.1, U5.6 (GND)
BAT_MONIT: C8.1, R10.1, R12.2, U4.12 (IO8)
BUTTON_ADC_1: C27.2, R4.1, R18.2, R19.2, R20.2, R60.2, U4.39 (IO1)
BUTTON_ADC_2: C28.2, R11.2, R28.1, R35.2, R36.2, R61.2, U4.4 (IO4)
C-: D8.1 (A1), J3.2, J6.11, Q6.3 (D), R49.1, TP4.1
CC1: J1.A5 (CC1), R3.1, U6.4
CC2: J1.B5 (CC2), R2.1, U6.3
CHRG: R67.1, U11.3 (~CHG)
COLOR_SEL: Q5.1 (G), R75.1, U4.33 (IO40), U12.2
DN: J1.A7 (D-), J1.B7 (D-), U4.13 (USB_D-), U6.1
DP: J1.A6 (D+), J1.B6 (D+), U4.14 (USB_D+), U6.6
EINK_3V3: C10.2, C22.2, F6.2, J2.15, J2.16, L1.2
EINK_SW: C11.2, D5.2 (A), L1.1, Q4.3 (D)
EPD_BUSY: J2.9, R34.1
EPD_CS: J2.12, R31.1
EPD_DC: J2.11, R32.1
EPD_RST: J2.10, R5.1, R33.1
ESP32_EN: C5.1, R7.2, R63.2, U4.3 (EN)
ESP32_IO0: R13.2, R64.2, U4.27 (IO0)
GND: C3.2, C4.2, C5.2, C6.2, C8.2, C9.1, C10.1, C12.1, C13.1, C14.1, C15.1, C16.1, C17.1, C18.1, C19.1, C20.1, C21.2, C22.1, C23.2, C24.2, C25.1, C26.2, C27.1, C28.1, C29.2, C30.2, C31.2, C32.2, C33.2, C36.1, C37.1, C38.2, CR1.2 (GND), CR2.2 (GND), CR3.2 (GND), D3.2 (A2), D6.1 (K), D8.3 (common), H1.1, H2.1, H3.1, H4.1, H5.1, H6.1, J1.A1 (GND), J1.A12 (GND), J1.B1 (GND), J1.B12 (GND), J1.S1 (SHIELD), J2.8, J2.17, J2.S1 (SHIELD), J2.S2 (SHIELD__1), J3.S1 (SHIELD), J3.S2 (SHIELD), J4.1, J4.S1 (SHIELD), J4.S2 (SHIELD), J6.1, J6.4, J7.6 (VSS), J7.9 (SHIELD), Q2.2 (S), Q8.1 (G), R2.2, R3.2, R6.2, R10.2, R14.1, R15.1, R16.1, R37.2, R41.2, R49.2, R50.2, R51.2, R59.2, R73.1, R75.2, R76.2, R77.2, R82.1, R84.2, R85.2, R86.2, SW1.1, SW2.1, SW3.1, SW4.1, SW5.1, SW6.1, SW8.1, SW9.1, SW11.1, TH1.2, U1.2, U2.1 (GND), U3.2 (GND), U4.1 (GND), U4.40 (GND), U4.41 (GND), U6.2, U7.2, U8.2, U9.2, U10.4 (GND), U11.5 (GND), U12.3 (GND), U13.2 (VCC), U13.5 (GND), U14.2 (VSS), U14.3 (CLKOE)
I2C_SCL: J6.10, R45.1, R47.2, R52.1, U4.32 (IO39), U8.3, U13.8 (SCL), U14.7 (SCL)
I2C_SDA: J6.8, R46.1, R48.2, R58.1, U4.31 (IO38), U8.4, U13.7 (SDA), U14.8 (SDA)
J6_3V3: CR2.1 (I/O), F5.2, J6.7
LDO_IN: C4.1, F3.1, U2.2 (VOUT), U2.7 (VOUT), U3.1 (IN), U3.3 (EN)
LED_MONIT: C31.1, R39.2, R41.1, U4.38 (IO2)
LED_SW: C9.2, D3.1 (A1), J3.1, J3.5, J6.5, R39.1, TP3.1, U10.5 (VOUT)
unnamed: C2.2, R84.1
unnamed: C13.2, J2.20
unnamed: C15.2, J2.22
unnamed: C17.2, J2.5
unnamed: C18.2, J2.18
unnamed: C19.2, J2.19
unnamed: C20.2, J2.24
unnamed: D2.1 (K), R59.1
unnamed: C11.1, D4.1 (K), D6.2 (A)
unnamed: Q3.3 (D), R27.2
unnamed: Q3.1 (G), R56.1, R57.1
unnamed: Q5.2 (S), Q6.2 (S), R37.1, U10.3 (FB)
unnamed: Q7.1 (G), R40.1, R78.2
unnamed: Q8.3 (D), R27.1
unnamed: Q9.1 (G), R79.2, R80.2
unnamed: R11.1, SW4.2
unnamed: R18.1, SW3.2
unnamed: R19.1, SW8.2
unnamed: R20.1, SW9.2
unnamed: R35.1, SW5.2
unnamed: R36.1, R72.2, SW7.2
unnamed: R60.1, SW2.2
unnamed: R61.1, SW1.2
unnamed: R62.1, SW10.1
unnamed: R63.1, SW11.2
unnamed: R64.1, SW6.2
unnamed: R73.2, R74.2, SW7.1
unnamed: R68.2, U4.15 (IO3)
unnamed: R26.1, U4.5 (IO5)
unnamed: R25.1, U4.6 (IO6)
unnamed: R24.1, U4.7 (IO7)
unnamed: R29.2, U4.20 (IO12)
unnamed: R30.2, U4.21 (IO13)
unnamed: R31.2, U4.22 (IO14)
unnamed: R23.1, U4.8 (IO15)
unnamed: R22.1, U4.9 (IO16)
unnamed: R21.1, U4.10 (IO17)
unnamed: R32.2, U4.23 (IO21)
unnamed: R69.1, U4.26 (IO45)
unnamed: R65.1, U4.16 (IO46)
unnamed: R33.2, U4.24 (IO47)
unnamed: R34.2, U4.25 (IO48)
unnamed: C34.1, R16.2, U5.2 (CS)
unnamed: Q1.4, U5.3 (OC)
unnamed: Q1.6, U5.1 (OD)
unnamed: C7.1, R83.1, U5.5 (VCC)
unnamed: R6.1, U11.4 (ISET)
P+: C3.1, C26.1, F2.2, Q8.2 (S), R12.1, R83.2, U2.6 (VIN2), U11.2 (OUT)
PREVGH: C14.2, D5.1 (K), J2.21
PREVGL: C16.2, D4.2 (A), J2.23
PWM_LED: U4.35 (IO42), U10.2 (ADIM)
PWR_BUTTON: C29.1, R62.2, R72.1, R76.1, U4.11 (IO18)
RX: TP1.1, U4.36 (RXD0)
SD_ACTIVATE: R78.1, U4.18 (IO10)
SD_CLK: J7.5 (CLK), R24.2, U1.4
SD_CMD: J7.3 (CMD), R23.2, R55.1, U1.6
SD_DAT0: J7.7 (DAT0), R8.1, R25.2, U9.3
SD_DAT1: J7.8 (DAT1), R9.1, R26.2, U9.1
SD_DAT2: J7.1 (DAT2), R21.2, R53.1, U1.3
SD_DAT3: J7.2 (DAT3/CD), R22.2, R54.1, U1.1
SD_VDD: C36.2, C37.2, J7.4 (VDD), Q7.3 (D), R8.2, R9.2, R53.2, R54.2, R55.2, R77.1
SPI_MOSI: J2.14, R29.1
SPI_SCK: J2.13, R30.1
ST: R17.1, U2.8 (ST)
TPS_SW_NODE: L2.2, U10.6 (SW)
TP_INT: R43.1, R44.1, U4.34 (IO41)
TP_RST: J4.3, U4.19 (IO11), U7.3
TS: C38.1, Q2.3 (D), R82.2, TH1.1, U11.1 (TS)
TX: TP2.1, U4.37 (TXD0)
UNUSED_GPIO_3: J6.9, R68.1, U8.6
UNUSED_GPIO_45: J6.3, R69.2, U8.1
UNUSED_GPIO_46: J6.2, R65.2, U9.6
USB_STAT: C23.1, R17.2, R67.2, R70.1, U4.17 (IO9)
USB_VBUS: C2.1, C25.2, D2.2 (A), F1.2, R38.1, R81.2, U2.3 (VIN1), U2.5 (MODE), U11.6 (VIN)
VBUS_PRE_FUSE: CR1.1 (I/O), F1.1, J1.A4 (VBUS), J1.A9 (VBUS), J1.B4 (VBUS), J1.B9 (VBUS)
W-: D8.2 (A2), J3.6, J6.6, Q5.3 (D), R50.1, TP5.1

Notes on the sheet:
Overcharge/Discharge Protection
ratio will be 0.5
USB / CHARGE STATUS ADC DIVIDER NOTE: Monitors TPS2116 ST and BQ21040 CHG via single ADC pin (USB_STAT). Draw: 1.1 uA on battery, < 3 uA on USB. High-Z node + C23: ~0.5 s to settle. PRIMARY OPERATIONAL STATES: 1) Discharging / Unplugged (VIN2 Active): ~2.20 V [Window: 1.80 V - 2.60 V] 2) Plugged in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
SDMMC Interface
LED lit when USB is plugged in 1.5mA at 2.0Vf (5 − 2.0)/0.0015 ≈ 2 kΩ
Battery<->USB Power Path Switch
RIGHT LEFT CONFIRM BACK
3.7V LiPo Battery Connector
Charge Pump
LED Driver & Connector
External RTC
0.1u cap placed near ESP32
Touch Connector + ESD
Touch Jumper Mux
Interface Buttons
ratio will be 0.107
3.3V min -> 1.65V
- +
VLS252012HBX-100M-1
2.2n cap placed near ESP32
pull-up on RST recommended to avoid epd wakes when in deep sleep
HIGH-Z = USB LOW = BATTERY
POWER GATE: SD_ACTIVATE gates VDD to the SD card SD_ACTIVATE HIGH (default) = OFF SD_ACTIVATE LOW = ON All data signals pulled up to SD_VDD All data signals should be asserted low before shutting down
External Peripheral Connector
External Peripheral ESD Protection
E-ink Driver & Connector
ESD Protection
Battery Charger
Typical Configuration used on 4.26"
ESP32 Pin-out
1u cap placed at ESP32
Reverse polarity protection
4.2V max -> 2.1V
ZIF 24-pin Connector
Local Pull-ups
DOWN(1) UP(1) DOWN(2) UP(2)
LDO 3.3V
USB Status
Power Button
High resistor values -> low idle current

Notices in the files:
README.md:
Licence:
The hardware is licensed under the **CERN Open Hardware Licence Version 2, Strongly Reciprocal
(CERN-OHL-S-2.0)**. See [LICENSE](LICENSE). What that means:
- **You may build this board, use it, modify it and sell it**, including commercially. You do not
need to ask.
- **If you distribute or sell a board based on this design, you must make your design source
available under the same CERN-OHL-S v2 licence**, and pass on the copyright and licence notice,
including any changes you made. That is what "strongly reciprocal" means.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
> Copyright © 2026 idc LLC.
